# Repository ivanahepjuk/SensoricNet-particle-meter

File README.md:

# SensoricNet-particle-meter

Check sensoricnet.com website [here](https://www.sensoricnet.com).

*ALL FILES IN THIS SensoricNet-Particle-Meter REPOSITORY ARE PUBLISHED UNDER GNU GENERAL PUBLIC LICENSE Version 3, 29 June 2007*

This is repo for sensoricnet, project backed by Vodafone. Nb-Iot stuff.

# Firmware
Please go to the firmware folder

# Hardware
Please go to HW folder

# Backend
Plese go to TBD

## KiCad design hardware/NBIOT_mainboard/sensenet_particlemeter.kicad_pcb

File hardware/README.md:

## Hardware plans

Created in KiCAD 5.0.2

##### SENSORICNET mother board version 1.0

* Core MCU STM32F072RBT6 (128kB memory)
* Communication by Quectel BC-95 NbIOT modem
* NanoSIM socket
* MOLEX PicoClasp connector for ALPHASENSE OPC-N2 (or OPC-N3) particle meter sensor
* GPS module Antennova M10578-A2, external antenna 
* ATECC508A secure element with internal cryptographic support for data validation, encrypting/decrypting, secure key storage
* RESET button, MODE button, three status LED's, one GPS FIX LED
* Prepared for 6V/500mA power source, variable connector (based on boxing)
* OLED 128x64 SSD1306 BW display
* Pin description added
* Added socket for BME280, it can be placed externally - improved accuracy 

OUTER SIDE:

.png)

INNER SIDE:

.png)

##### SENSORICNET LORAWAN shield

* Enhancement for SENSORICNET Motherboard
* Lorawan modem Microchip RN2483
* all pins form motherboard fit through this shield, possibility for adding another one

OUTER SIDE:

.png)

INNER SIDE:

.png)

##### SENSORICNET shield template
* Allows anybody to quickly develop own sensing shield for SENSORICNET
* Do you have an idea how to upgrade our sensor? Creating a shield sounds like a good way!

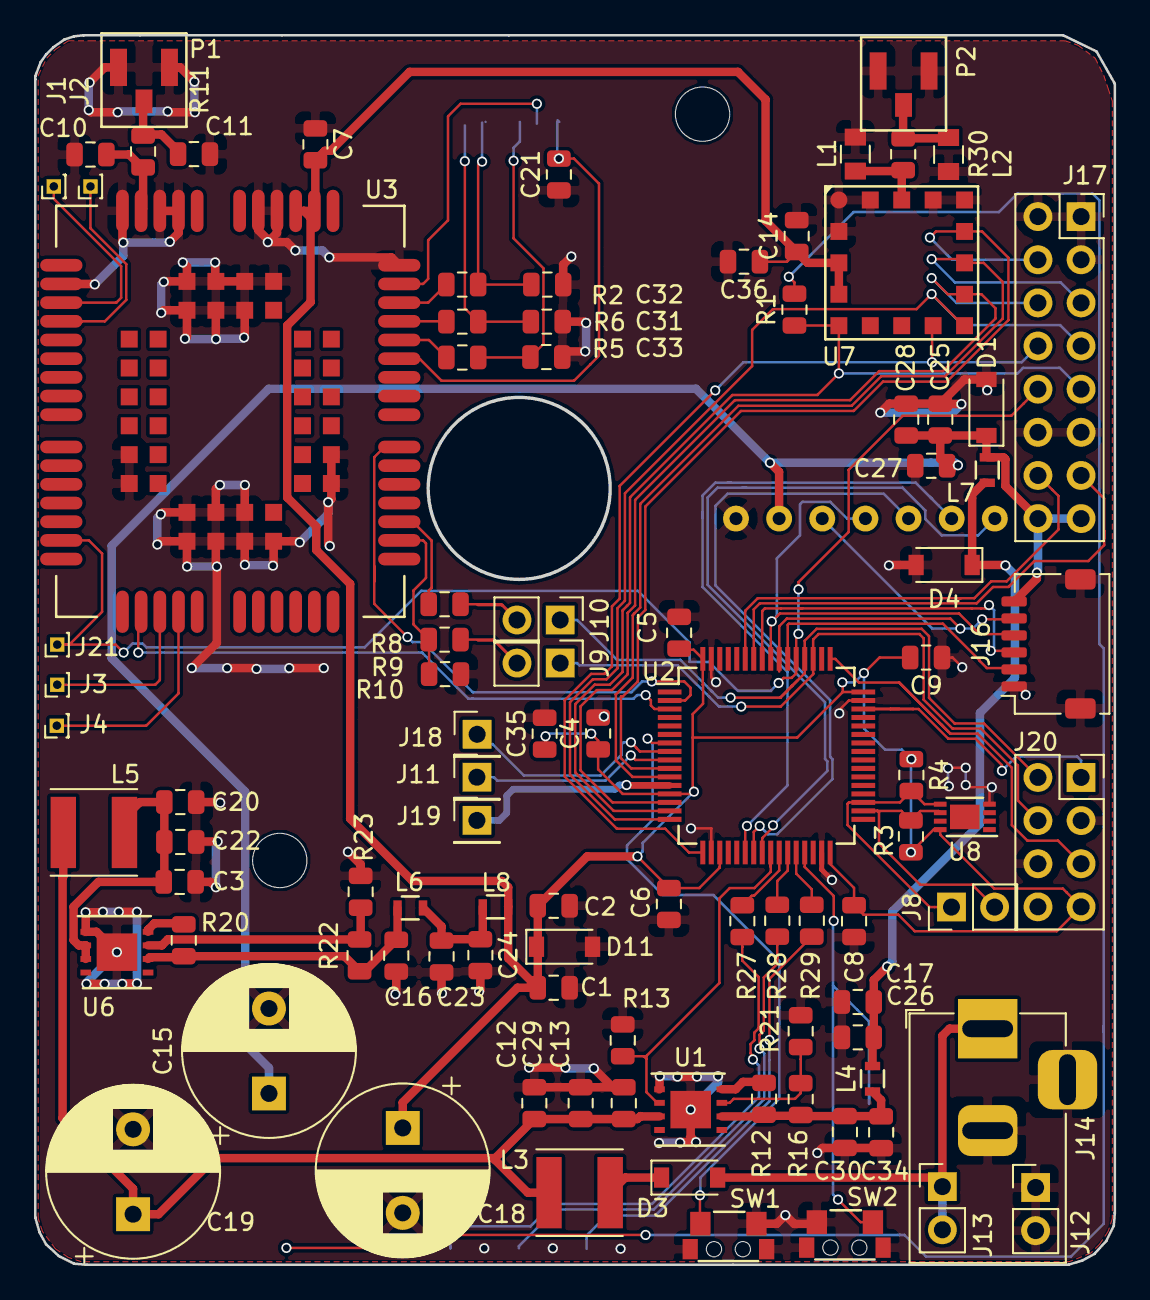
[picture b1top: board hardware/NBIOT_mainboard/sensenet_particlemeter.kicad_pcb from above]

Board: 2 copper layers, 63.6 x 72.4 mm, 106 parts (0 on the bottom side), 72 nets.

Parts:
C1, C4, C5, C6, C7, C8, C9, C12, C17, C20, C21, C23, C25, C36: 100n; C_0805_2012Metric
C2, C28: 22p; C_0805_2012Metric
C3, C13: 22u; C_0805_2012Metric
C10, C11: DNP; C_0805_2012Metric
C14: 2,2u; C_0805_2012Metric
C15, C19: 470u; CP_Radial_D10.0mm_P5.00mm
C16, C30, C34: 47u; C_0805_2012Metric
C18: 470uF; CP_Radial_D10.0mm_P5.00mm
C22, C24, C26, C27, C29, C35: 1n; C_0805_2012Metric
C31, C32, C33: 33p; C_0805_2012Metric
D1, D4: PTVS3V3S1UR,115; D_SOD-123
D2, D10: LED GREEN; SMD_0805_bottom
D3: D_Schottky_ss14; D_SOD-123
D8: LED RED; SMD_0805_bottom
D9: LED YELLOW; SMD_0805_bottom
D11: SM2T3V3A; D_SOD-123
J1, J2, J3, J4, J21: CONN_01X01; Pin_Header_Straight_1x01_Pitch1.00mm
J5, J6: CONN_01X01; MountingHole_3.2mm_M3_DIN965
J7: Conn_01x07_Female; OLED
J8, J9, J10: Conn_02x01; PinHeader_1x02_P2.54mm_Vertical
J11, J18, J19: CONN_01X01; Pin_Header_Straight_1x01_Pitch2.54mm
J12: Barrel_Jack_Switch; BarrelJack_Horizontal
J13, J14: Conn_01x02_Female; PinHeader_1x02_P2.54mm_Vertical
J16: Conn_01x06_Female; pico_clasp_6_horizontal
J17: Conn_02x08_Odd_Even; PinSocket_2x08_P2.54mm_Vertical
J20: Conn_02x04_Odd_Even; PinSocket_2x04_P2.54mm_Vertical
L1, L2: DNP; SMD_0805
L3: 39uH; L_Taiyo-Yuden_NR-50xx
L4, L6, L7, L8: FBMH1608HL601-T; R_0603
L5: 41uH; L_Taiyo-Yuden_NR-50xx
LOGO1: LOGO; PCB_artwork
LOGO2: LOGO; OSHW-Logo2_9.8x8mm_BackSilkScreen
P1, P2: SMA_mini; Antenna_conn
R1, R8, R9, R23, R27, R28, R29: 1k; R_0805_2012Metric
R2, R5, R6: 22R; R_0805_2012Metric
R3, R4: 4k7; R_0805_2012Metric
R10: 10k; R_0805_2012Metric
R11, R30: 0R; R_0805_2012Metric
R12, R13, R20: 100k; R_0805_2012Metric
R16: 3k3; R_0805_2012Metric
R21: 1k1; R_0805_2012Metric
R22: 1k6; R_0805_2012Metric
SW1, SW2: SW_DPST; edge_switch
U1, U6: NCP59152; DFN-8-1EP_4x4mm_P0.8mm_EP2.39x2.21mm
U2: stm32f072; TQFP-64_10x10mm_Pitch0.5mm
U3: QUECTEL_BC95; quectel_BC95
U4: SIM; nanosimmm
U7: M10578-A2; M10578
U8: ATECC508A; DFN-8-1EP_3x2mm_P0.5mm_EP1.75x1.45mm

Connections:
5V_enable: R13.1, U1.2, U2.25
+3V3: C1.1, C2.1, C4.1, C5.2, C6.1, C7.2, C8.1, C9.2, C14.1, C18.1, C35.1, C36.1, D11.1, J20.7, L8.1, R3.1, R4.1, U2.13, U2.19, U2.32, U2.48, U2.64, U3.45, U3.46, U7.14, U7.15, U8.8
+5V: C15.1, C25.1, C27.1, C28.1, D1.1, J7.2, J16.6, J17.15, J17.16, L7.1
+6V: C12.1, C13.1, C19.1, C29.1, L3.2, L5.1, U1.3
+9V: D3.2, J12.1, J13.1, J13.2
GND: C1.2, C2.2, C3.2, C4.2, C5.1, C6.2, C7.1, C8.2, C9.1, C10.1, C11.1, C12.2, C13.2, C14.2, C15.2, C16.2, C17.2, C18.2, C19.2, C20.2, C21.1, C22.2, C23.2, C24.2, C25.2, C26.2, C27.2, C28.2, C29.2, C30.2, C31.1, C32.1, C33.1, C34.2, C35.2, C36.2, D1.2, D2.1, D4.2, D8.1, D9.1, D10.1, D11.2, J7.1, J12.2, J12.3, J14.1, J14.2, J16.1, J17.1, J17.2, J17.3, J17.11, J17.12, J20.3, J20.6, J20.8, L1.2, L2.2, P1.1, P1.3, P2.1, P2.3, R10.1, R13.2, R21.2, R23.2, SW1.1, SW1.3, SW1.4, SW2.2, SW2.3, SW2.4, U1.1, U1.9, U2.18, U2.31, U2.47, U2.63, U3.2, U3.43, U3.47, U3.48, U3.51, U3.52, U3.54, U3.59, U3.60, U3.61, U3.62, U3.63, U3.64, U3.65, U3.66, U3.71, U3.72, U3.73, U3.74, U3.81, U3.82, U3.83, U3.92, U3.93, U3.94, U6.1, U6.9, U7.1, U7.2, U7.4, U7.5, U7.16, U8.4
NETLIGHT: U2.3, U3.18
unnamed: C10.2, R11.2, U3.53
unnamed: C11.2, P1.2, R11.1
unnamed: C16.1, L6.2, R20.2, R22.1, U6.6
unnamed: C17.1, C26.1, D4.1, L4.1, L7.2
unnamed: C3.1, C20.1, C22.1, L5.2, U6.2, U6.3
unnamed: C21.2, U3.38, U4.6
unnamed: C23.1, C24.1, L6.1, L8.2
unnamed: C30.1, C34.1, L4.2, R12.1, R16.1, U1.6
unnamed: C31.2, R6.1, U4.1
unnamed: C32.2, R2.1, U4.2
unnamed: C33.2, R5.1, U4.4
unnamed: D2.2, R1.2
unnamed: D3.1, L3.1
unnamed: D8.2, R27.2
unnamed: D9.2, R28.2
unnamed: D10.2, R29.2
unnamed: J1.1, U3.3
unnamed: J2.1, U3.4
unnamed: J3.1, U3.19
unnamed: J4.1, U3.20
unnamed: J9.2, R9.1
unnamed: J10.2, R8.1
unnamed: J11.1, U2.9
unnamed: J18.1, U2.8
unnamed: J19.1, U2.12
unnamed: L1.1, R30.2, U7.3
unnamed: L2.1, P2.2, R30.1
unnamed: R2.2, U3.41
unnamed: R5.2, U3.39
unnamed: R6.2, U3.40
unnamed: R8.2, U3.30
unnamed: R9.2, R10.2, U3.29
unnamed: R12.2, U1.8
unnamed: R16.2, R21.1, U1.7
unnamed: R20.1, U6.8
unnamed: R22.2, R23.1, U6.7
unnamed: R27.1, U2.26
unnamed: R28.1, U2.27
unnamed: R29.1, U2.28
unnamed: SW1.2, U2.7
unnamed: SW2.1, U2.29
unnamed: U3.42, U4.5
OLED_CS: J7.7, U2.24
OLED_D/C: J7.6, U2.22
OLED_RESET: J7.5, U2.23
PM_SCK: J7.3, J16.5, U2.55
PM_SDI: J16.3, U2.57
PM_SDO: J7.4, J16.4, U2.56
PM_SS: J16.2, U2.54
RI: U2.2, U3.34
Rx: J10.1, J20.2, U2.52
SWD_CLK: J20.5, U2.49
SWD_DIO: J20.1, U2.46
Tx: J9.1, J20.4, U2.51
UART_GPS_RX: J17.8, U2.17, U7.10
UART_GPS_TX: J17.7, U2.16, U7.9
USART_debug_rx: J17.14, U2.59
USART_debug_tx: J17.13, U2.58
WIRELESS_reset: J17.10, J21.1, U2.53, U3.15
gps_fix: J17.9, R1.1, U2.15, U7.13
gps_pulses: J17.4, U2.10, U7.6
gps_reset: J17.5, U2.11, U7.7
gps_standby: J17.6, U2.14, U7.8
i2c_scl: J8.2, R3.2, U2.34, U8.6
i2c_sda: J8.1, R4.2, U2.35, U8.5

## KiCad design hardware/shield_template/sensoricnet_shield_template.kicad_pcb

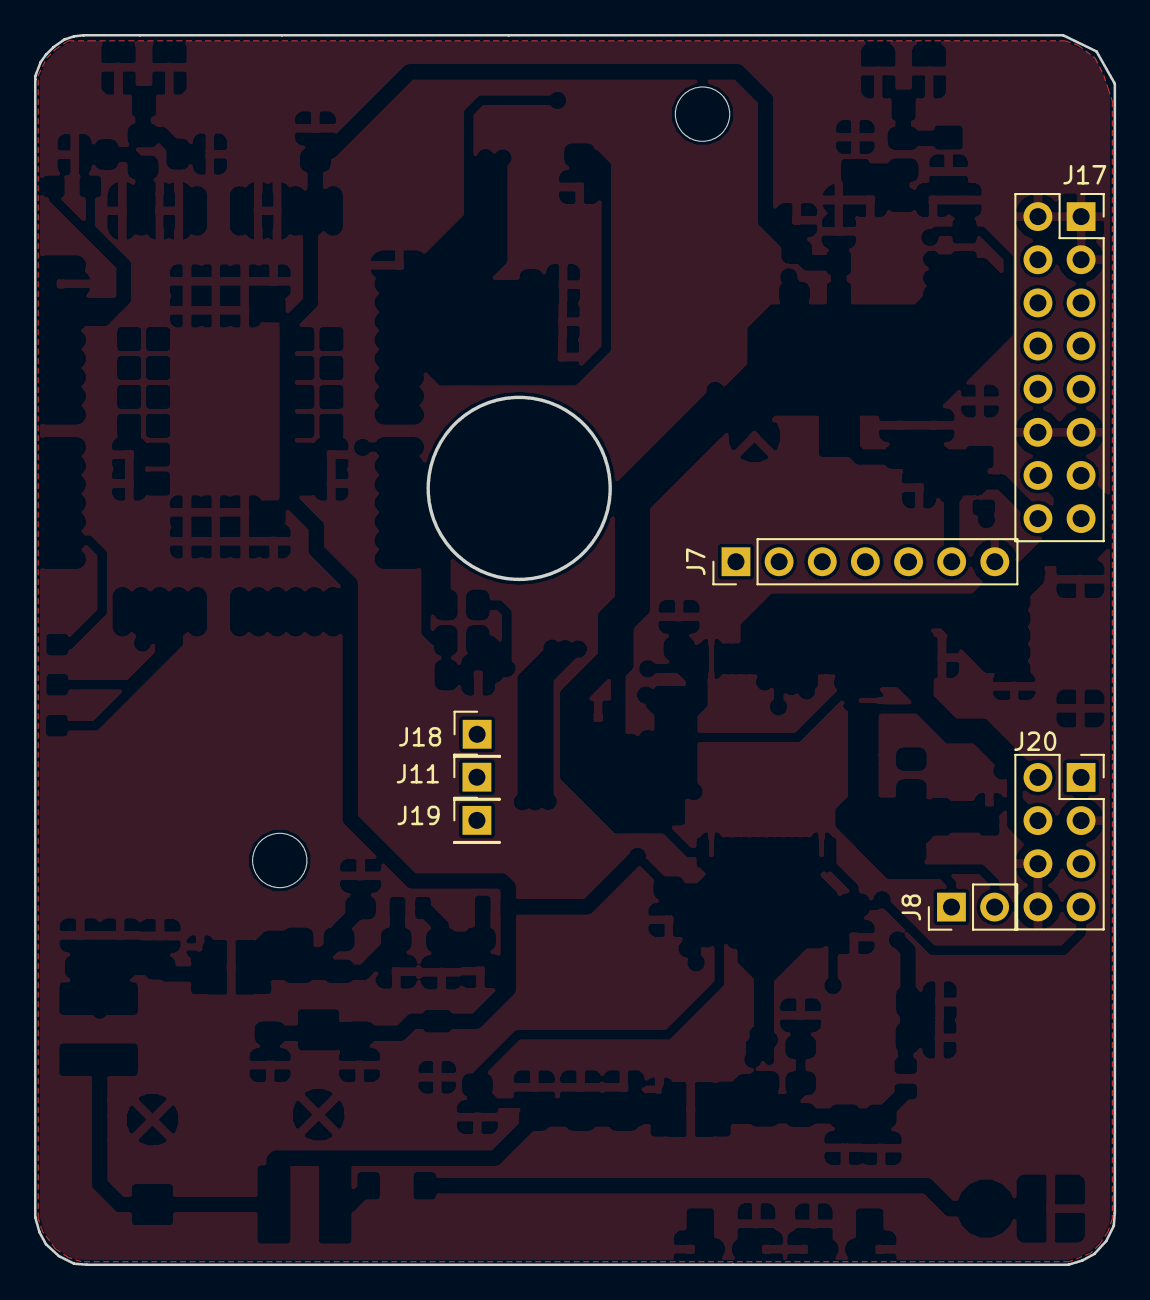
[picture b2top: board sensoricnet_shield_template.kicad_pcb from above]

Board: 2 copper layers, 63.6 x 72.4 mm, 10 parts (0 on the bottom side), 2 nets, no tracks yet.

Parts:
J5, J6: Conn_01x01_Female; MountingHole_3.2mm_M3_DIN965
J7: Conn_01x07_Female; PinHeader_1x07_P2.54mm_Vertical
J8: Conn_02x01; PinHeader_1x02_P2.54mm_Vertical
J11, J18, J19: CONN_01X01; Pin_Header_Straight_1x01_Pitch2.54mm
J17: Conn_02x08_Odd_Even; PinSocket_2x08_P2.54mm_Vertical
J20: Conn_02x04_Odd_Even; PinSocket_2x04_P2.54mm_Vertical
LOGO1: LOGO; PCB_artwork

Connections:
+5V: J7.6, J17.15, J17.16
GND: J7.7, J17.1, J17.2, J17.3, J17.11, J17.12, J20.3, J20.6, J20.8

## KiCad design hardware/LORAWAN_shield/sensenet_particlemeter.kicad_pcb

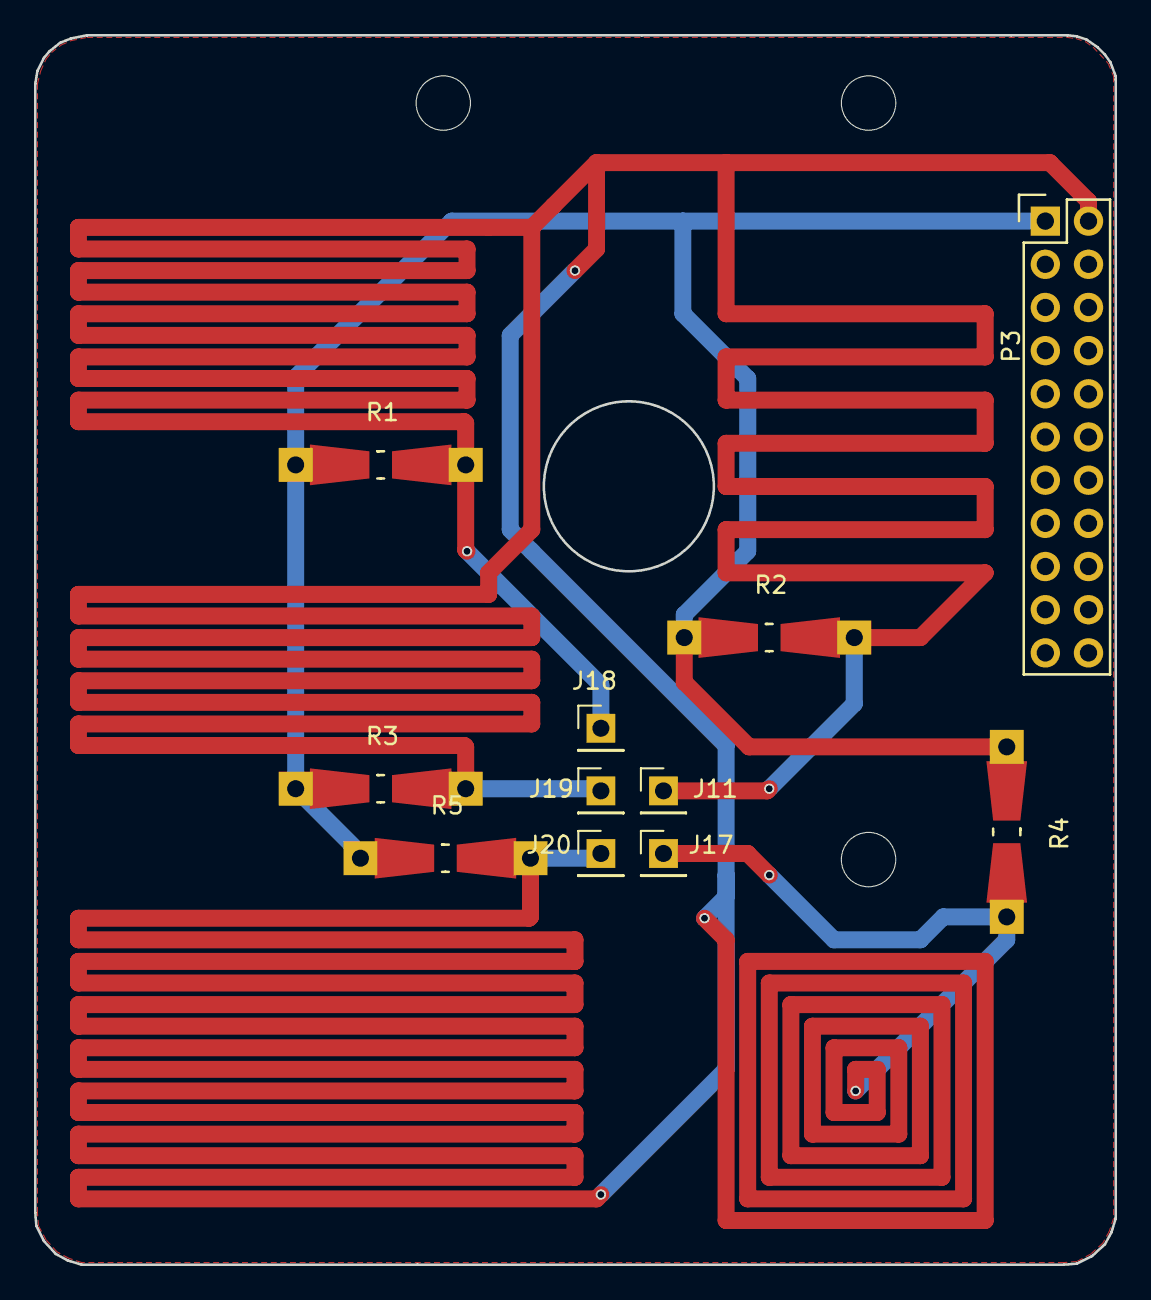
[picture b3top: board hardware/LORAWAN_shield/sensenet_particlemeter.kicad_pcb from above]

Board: 2 copper layers, 63.6 x 72.3 mm, 14 parts (0 on the bottom side), 2 nets.

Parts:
J5, J6, J9: CONN_01X01; MountingHole_3.2mm_M3_DIN965
J11, J17, J18, J19, J20: CONN_01X01; Pin_Header_Straight_1x01_Pitch2.54mm
P3: CONN_02X11; Pin_Header_Straight_2x11
R1, R2, R3, R4, R5: R; Resistor_SMD+THTuniversal_0805to1206_RM10_HandSoldering

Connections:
+3V3: P3.1, R1.1, R2.1, R3.1, R4.1, R5.1
GND: J11.1, J17.1, J18.1, J19.1, J20.1, P3.2, R1.2, R2.2, R3.2, R4.2, R5.2

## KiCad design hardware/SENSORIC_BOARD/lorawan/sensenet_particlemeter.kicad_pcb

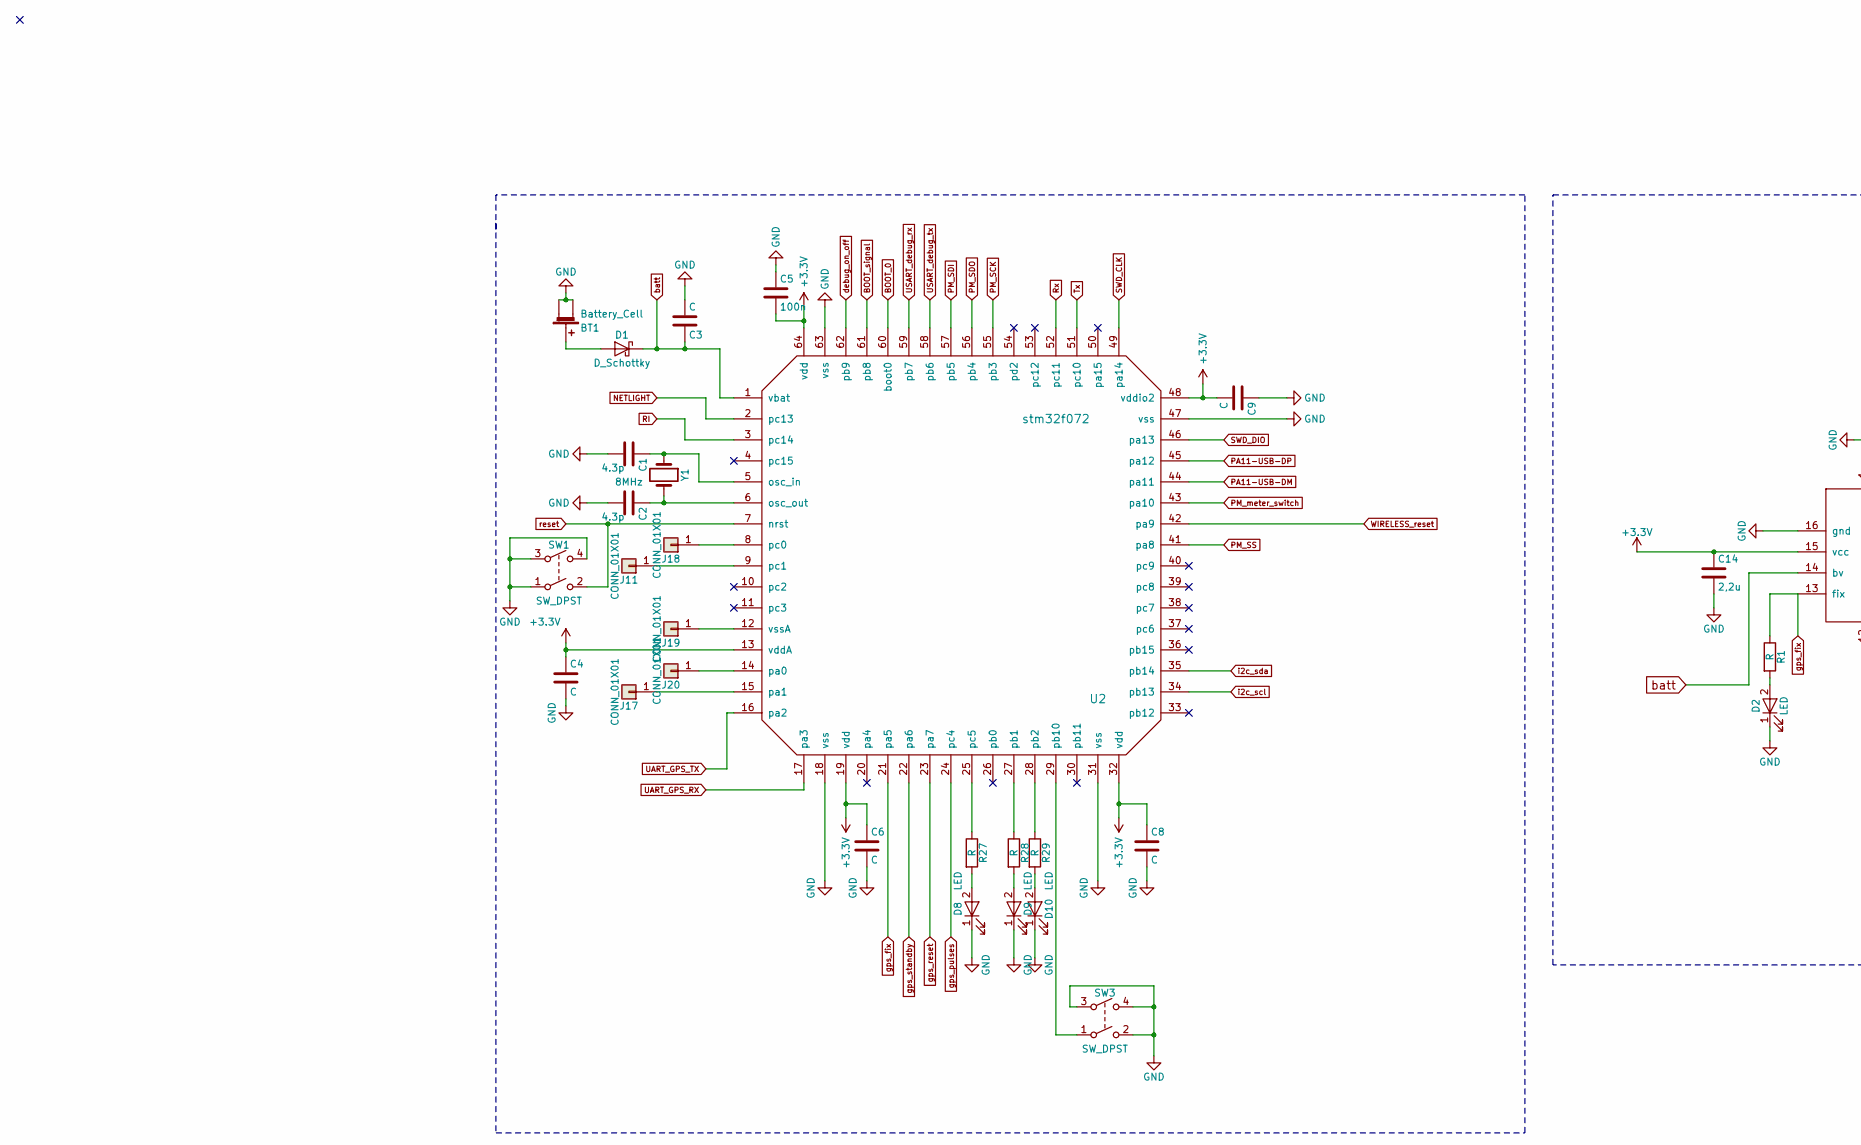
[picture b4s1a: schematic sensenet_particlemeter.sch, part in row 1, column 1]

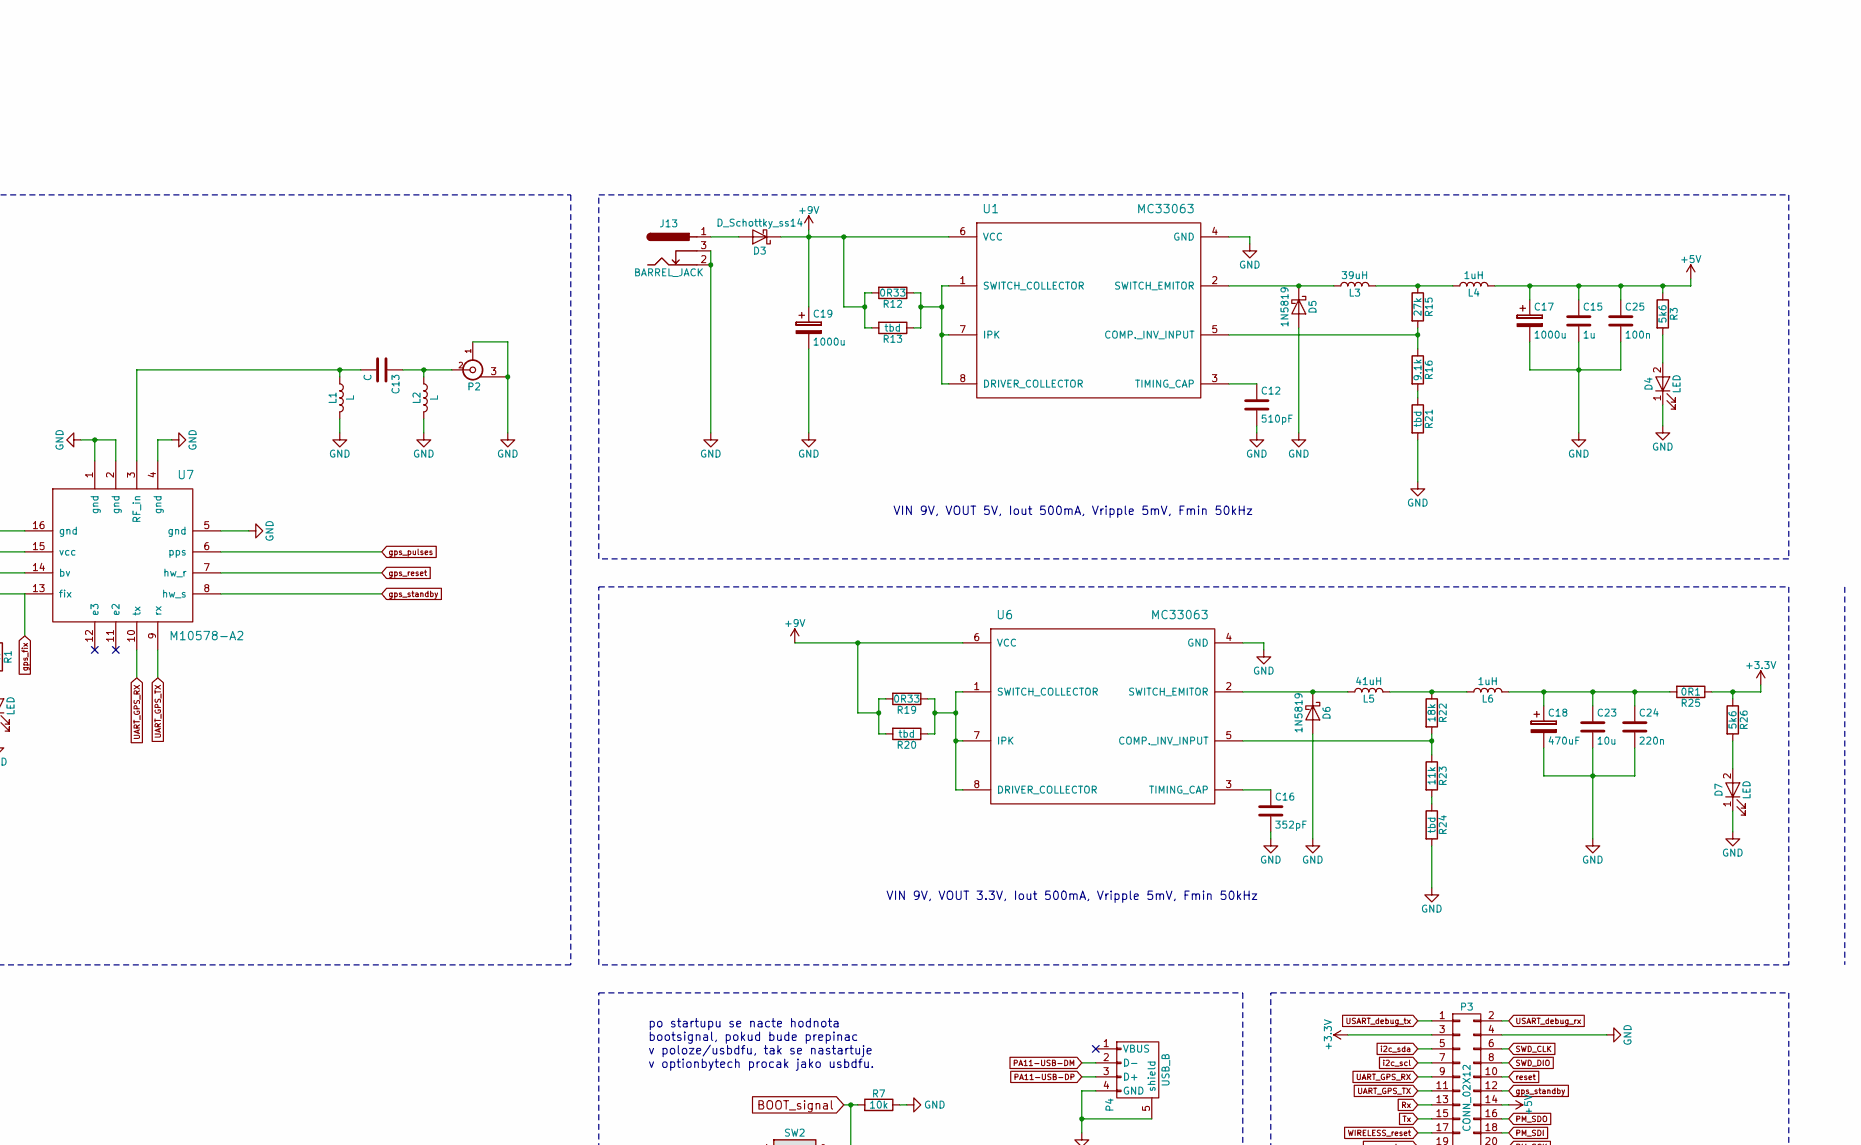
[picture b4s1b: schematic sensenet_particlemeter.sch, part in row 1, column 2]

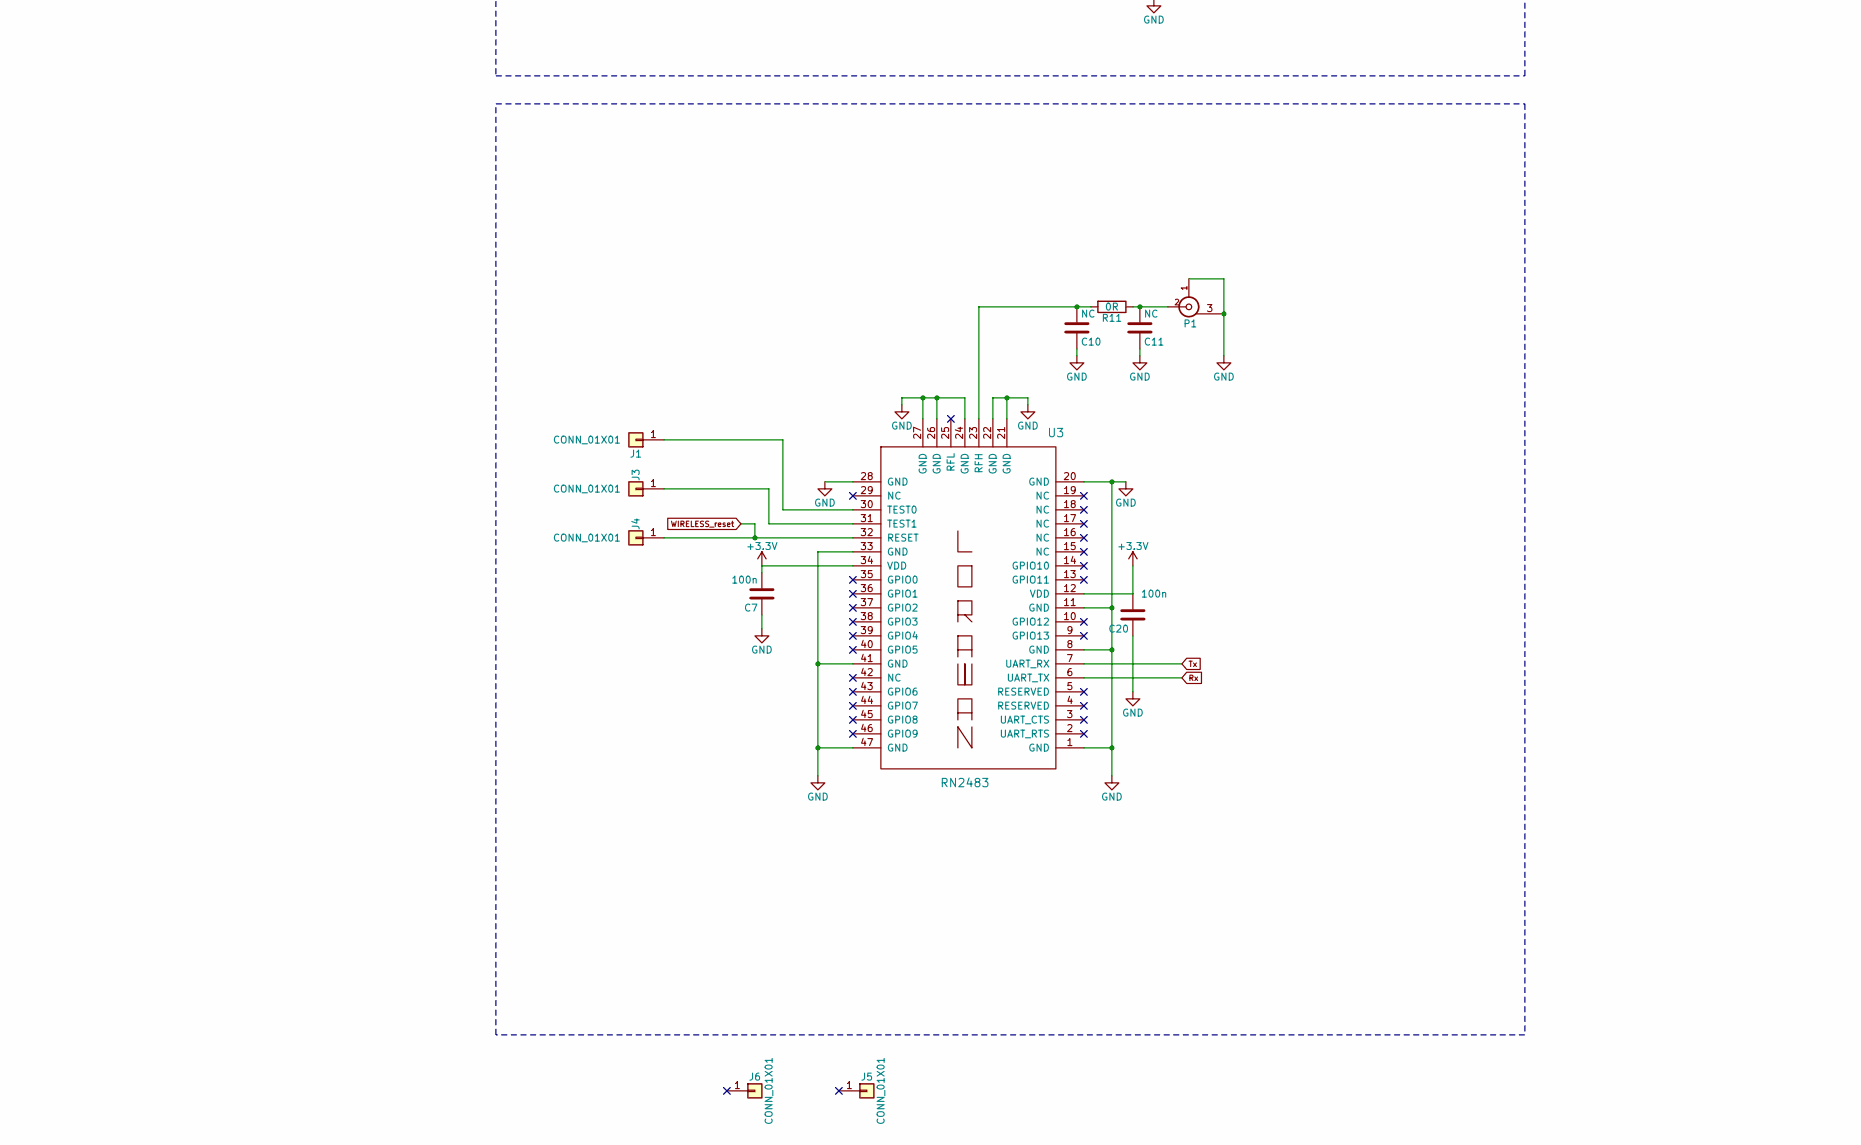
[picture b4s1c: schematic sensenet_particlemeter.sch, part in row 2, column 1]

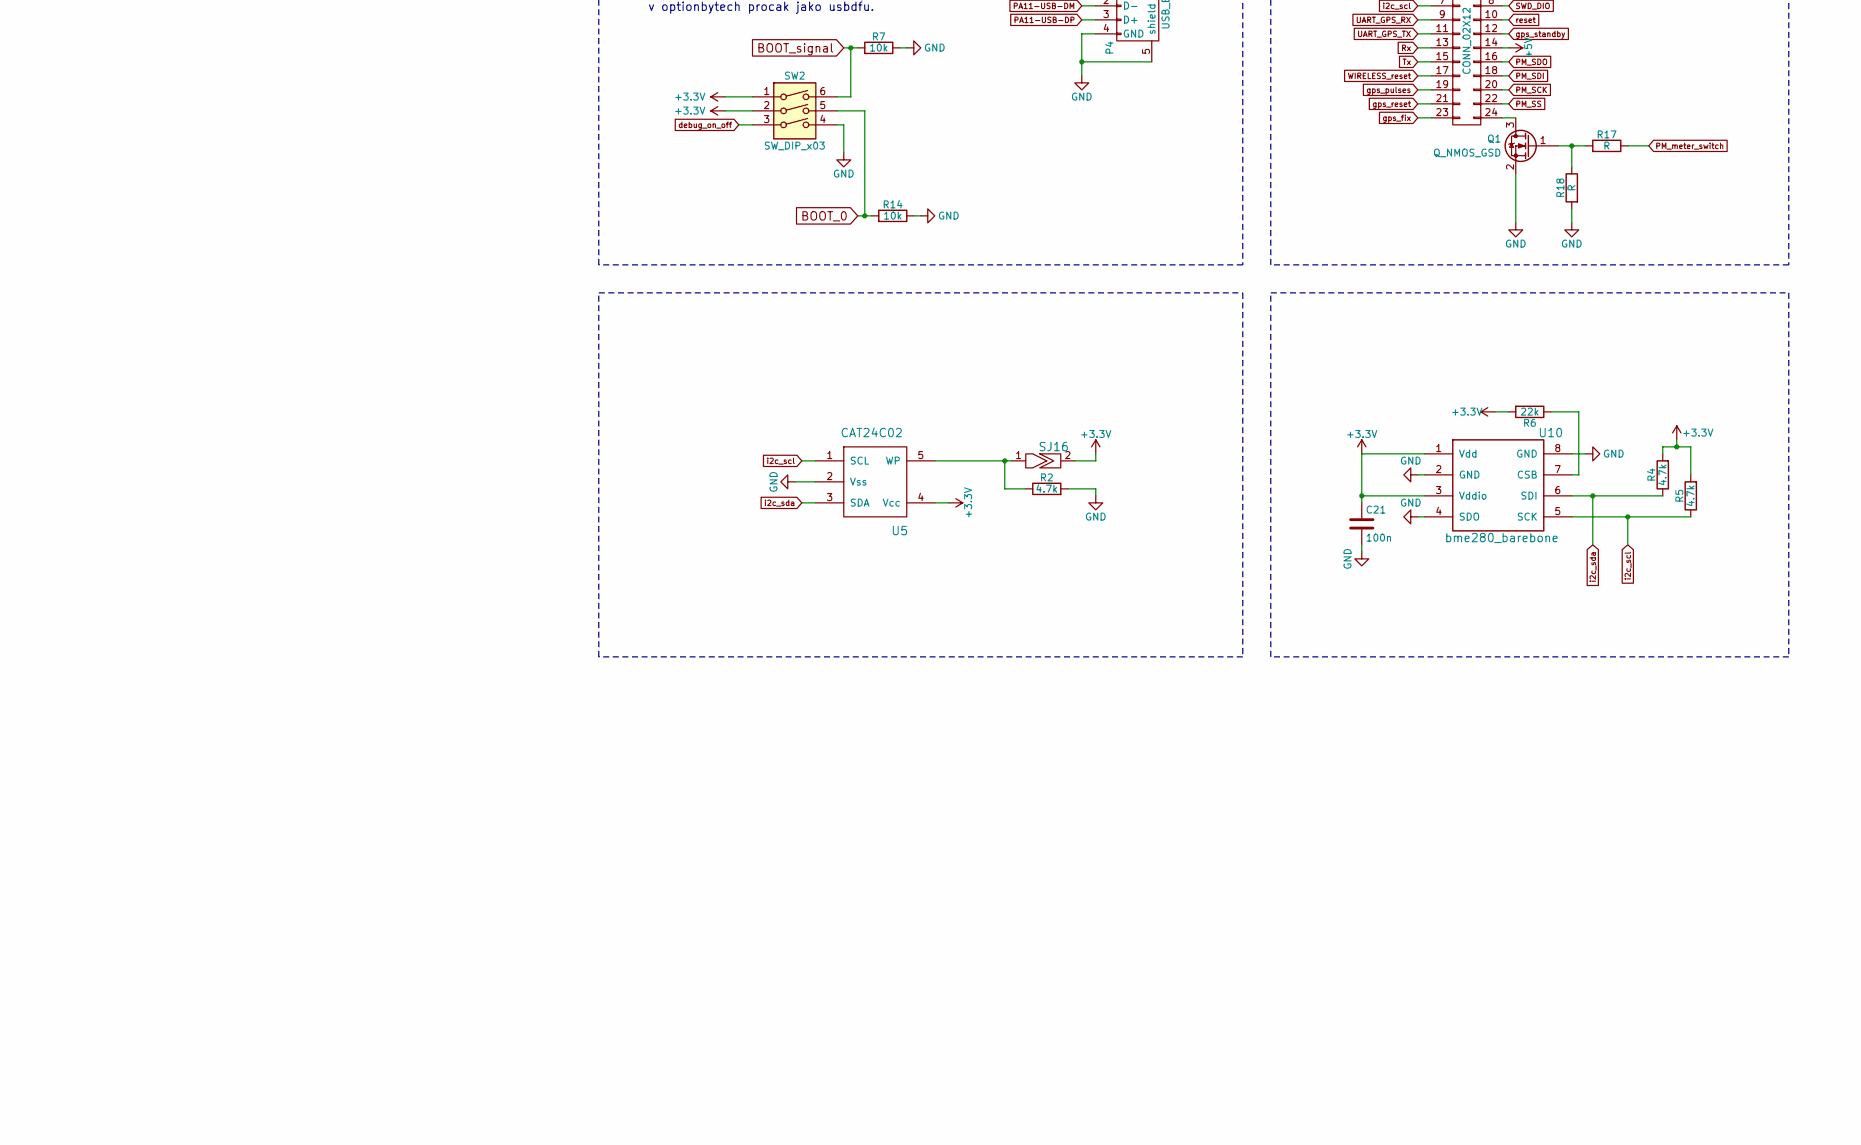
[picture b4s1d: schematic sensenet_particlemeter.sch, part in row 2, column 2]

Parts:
BT1: Battery_Cell; BAT-CR2032_bottom
C1, C2: 4.3p; SMD_0805
C3, C4, C6, C8, C9, C13: C; SMD_0805
C5, C7, C20, C21, C25: 100n; SMD_0805
C10, C11: NC; SMD_0805
C12: 510pF; SMD_0805
C14: 2,2u; SMD_0805
C15: 1u; SMD_0805
C16: 352pF; SMD_0805
C17, C19: 1000u; C_Radial_D10_L16_P5_bottom
C18: 470uF; C_Radial_D6.3_L11.2_P2.5_bottom
C23: 10u; SMD_0805
C24: 220n; SMD_0805
D1: D_Schottky; D_SOD-123
D2, D4, D7, D8, D9, D10: LED; SMD_0805
D3: D_Schottky_ss14; D_SOD-123
D5, D6: 1N5819; SOD-123
J1, J3, J4: CONN_01X01; Pin_Header_Straight_1x01_Pitch1.00mm
J5, J6: CONN_01X01; MountingHole_3.2mm_M3_DIN965
J11, J17, J18, J19, J20: CONN_01X01; Pin_Header_Straight_1x01_Pitch2.54mm
J13: BARREL_JACK
L1, L2: L; SMD_0805
L3: 39uH; Inductor_Taiyo-Yuden_NR-50xx
L4, L6: 1uH; SMD_0805
L5: 41uH; Inductor_Taiyo-Yuden_NR-50xx
P1, P2: SMA_mini; Antenna_conn
P3: CONN_02X12; Pin_Header_Straight_2x12
P4: USB_B; USB_Micro-B
Q1: Q_NMOS_GSD; SOT-23
R1, R17, R18, R27, R28, R29: R; SMD_0805
R2, R4, R5: 4.7k; SMD_0805
R3, R26: 5k6; SMD_0805
R6: 22k; SMD_0805
R7, R14: 10k; SMD_0805
R11: 0R; SMD_0805
R12, R19: 0R33; SMD_0805
R13, R20, R21, R24: tbd; SMD_0805
R15: 27k; SMD_0805
R16: 9.1k; SMD_0805
R22: 18k; SMD_0805
R23: 11k; SMD_0805
R25: 0R1; SMD_0805
SJ16: solder_jumper
SW1, SW3: SW_DPST; edge_switch
SW2: SW_DIP_x03; DIP-6_W7.62mm
U1, U6: MC33063; SOIC-8_3.9x4.9mm_Pitch1.27mm
U2: stm32f072; TQFP-64_10x10mm_Pitch0.5mm
U3: RN2483; RN2483_top
U5: CAT24C02; SOT-23-5
U7: M10578-A2; M10578
U10: bme280_barebone; BME280
Y1: 8MHz; Crystal_SMD_5032-2pin_5.0x3.2mm

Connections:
+3V3: C4.1, C5.2, C6.1, C7.2, C8.1, C9.2, C14.1, C20.2, C21.1, P3.3, R4.2, R5.2, R6.2, R25.1, R26.1, SJ16.2, SW2.1, SW2.2, U2.13 (vddA), U2.19 (vdd), U2.32 (vdd), U2.48 (vddio2), U2.64 (vdd), U3.12 (VDD), U3.34 (VDD), U5.4 (Vcc), U7.15 (vcc), U10.1 (Vdd), U10.3 (Vddio)
+5V: C15.1, C17.1, C25.1, L4.2, P3.14, R3.1
+9V: C19.1, D3.1 (K), R12.2, R13.2, R19.2, R20.2, U1.6 (VCC), U6.6 (VCC)
BOOT_0: R14.2, SW2.5, U2.60 (boot0)
BOOT_signal: R7.2, SW2.6, U2.61 (pb8)
GND: BT1.2 (-), BT1.3 (-), C1.2, C2.2, C3.2, C4.2, C5.1, C6.2, C7.1, C8.2, C9.1, C10.1, C11.1, C12.2, C14.2, C15.2, C16.2, C17.2, C18.2, C19.2, C20.1, C21.2, C23.2, C24.2, C25.2, D2.1 (K), D4.1 (K), D5.2 (A), D6.2 (A), D7.1 (K), D8.1 (K), D9.1 (K), D10.1 (K), J13.2, J13.3, L1.2, L2.2, P1.1 (gnd), P1.3 (gnd), P2.1 (gnd), P2.3 (gnd), P3.4, P4.4 (GND), P4.5 (shield), Q1.2 (S), R2.2, R7.1, R14.1, R18.2, R21.2, R24.2, SW1.1, SW1.3, SW1.4, SW2.4, SW3.2, SW3.3, SW3.4, U1.4 (GND), U2.18 (vss), U2.31 (vss), U2.47 (vss), U2.63 (vss), U3.1 (GND), U3.8 (GND), U3.11 (GND), U3.20 (GND), U3.21 (GND), U3.22 (GND), U3.24 (GND), U3.26 (GND), U3.27 (GND), U3.28 (GND), U3.33 (GND), U3.41 (GND), U3.47 (GND), U5.2 (Vss), U6.4 (GND), U7.1 (gnd), U7.2 (gnd), U7.4 (gnd), U7.5 (gnd), U7.16 (gnd), U10.2 (GND), U10.4 (SDO), U10.8 (GND)
unnamed: BT1.1 (+), D1.2 (A)
unnamed: C1.1, U2.5 (osc_in), Y1.1
unnamed: C2.1, U2.6 (osc_out), Y1.2
unnamed: C10.2, R11.2, U3.23 (RFH)
unnamed: C11.2, P1.2 (In), R11.1
unnamed: C12.1, U1.3 (TIMING_CAP)
unnamed: C13.1, L2.1, P2.2 (In)
unnamed: C13.2, L1.1, U7.3 (RF_in)
unnamed: C16.1, U6.3 (TIMING_CAP)
unnamed: C18.1, C23.1, C24.1, L6.2, R25.2
unnamed: D2.2 (A), R1.2
unnamed: D3.2 (A), J13.1
unnamed: D4.2 (A), R3.2
unnamed: D5.1 (K), L3.1, U1.2 (SWITCH_EMITOR)
unnamed: D6.1 (K), L5.1, U6.2 (SWITCH_EMITOR)
unnamed: D7.2 (A), R26.2
unnamed: D8.2 (A), R27.2
unnamed: D9.2 (A), R28.2
unnamed: D10.2 (A), R29.2
unnamed: J1.1, U3.30 (TEST0)
unnamed: J3.1, U3.31 (TEST1)
unnamed: J11.1, U2.9 (pc1)
unnamed: J17.1, U2.15 (pa1)
unnamed: J18.1, U2.8 (pc0)
unnamed: J19.1, U2.12 (vssA)
unnamed: J20.1, U2.14 (pa0)
unnamed: L3.2, L4.1, R15.1
unnamed: L5.2, L6.1, R22.1
unnamed: P3.24, Q1.3 (D)
unnamed: Q1.1 (G), R17.2, R18.1
unnamed: R2.1, SJ16.1, U5.5 (WP)
unnamed: R6.1, U10.7 (CSB)
unnamed: R12.1, R13.1, U1.1 (SWITCH_COLLECTOR), U1.7 (IPK), U1.8 (DRIVER_COLLECTOR)
unnamed: R15.2, R16.1, U1.5 (COMP._INV_INPUT)
unnamed: R16.2, R21.1
unnamed: R19.1, R20.1, U6.1 (SWITCH_COLLECTOR), U6.7 (IPK), U6.8 (DRIVER_COLLECTOR)
unnamed: R22.2, R23.1, U6.5 (COMP._INV_INPUT)
unnamed: R23.2, R24.1
unnamed: R27.1, U2.25 (pc5)
unnamed: R28.1, U2.27 (pb1)
unnamed: R29.1, U2.28 (pb2)
unnamed: SW3.1, U2.29 (pb10)
PA11-USB-DM: P4.2 (D-), U2.44 (pa11)
PA11-USB-DP: P4.3 (D+), U2.45 (pa12)
PM_SCK: P3.20, U2.55 (pb3)
PM_SDI: P3.18, U2.57 (pb5)
PM_SDO: P3.16, U2.56 (pb4)
PM_SS: P3.22, U2.41 (pa8)
PM_meter_switch: R17.1, U2.43 (pa10)
Rx: P3.13, U2.52 (pc11), U3.6 (UART_TX)
SWD_CLK: P3.6, U2.49 (pa14)
SWD_DIO: P3.8, U2.46 (pa13)
Tx: P3.15, U2.51 (pc10), U3.7 (UART_RX)
UART_GPS_RX: P3.9, U2.17 (pa3), U7.10 (tx)
UART_GPS_TX: P3.11, U2.16 (pa2), U7.9 (rx)
USART_debug_rx: P3.2, U2.59 (pb7)
USART_debug_tx: P3.1, U2.58 (pb6)
WIRELESS_reset: J4.1, P3.17, U2.42 (pa9), U3.32 (RESET)
batt: C3.1, D1.1 (K), U2.1 (vbat), U7.14 (bv)
debug_on_off: SW2.3, U2.62 (pb9)
gps_fix: P3.23, R1.1, U2.21 (pa5), U7.13 (fix)
gps_pulses: P3.19, U2.24 (pc4), U7.6 (pps)
gps_reset: P3.21, U2.23 (pa7), U7.7 (hw_r)
gps_standby: P3.12, U2.22 (pa6), U7.8 (hw_s)
i2c_scl: P3.7, R5.1, U2.34 (pb13), U5.1 (SCL), U10.5 (SCK)
i2c_sda: P3.5, R4.1, U2.35 (pb14), U5.3 (SDA), U10.6 (SDI)
reset: P3.10, SW1.2, U2.7 (nrst)

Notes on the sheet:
po startupu se nacte hodnota bootsignal, pokud bude prepinac v poloze/usbdfu, tak se nastartuje v optionbytech procak jako usbdfu.
VIN 9V, VOUT 5V, Iout 500mA, Vripple 5mV, Fmin 50kHz
VIN 9V, VOUT 3.3V, Iout 500mA, Vripple 5mV, Fmin 50kHz
